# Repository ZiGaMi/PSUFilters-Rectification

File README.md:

# PSUFilters-Rectification
This repository contains KiCad project of circuit with filtering, rectification and safety elements for PSU module. Purpose of circuit is to adjust mains voltage to working voltage of cheap PSU modules. In this case PSU module DP50V5A is used, but other modules can be used with same circuit as well.

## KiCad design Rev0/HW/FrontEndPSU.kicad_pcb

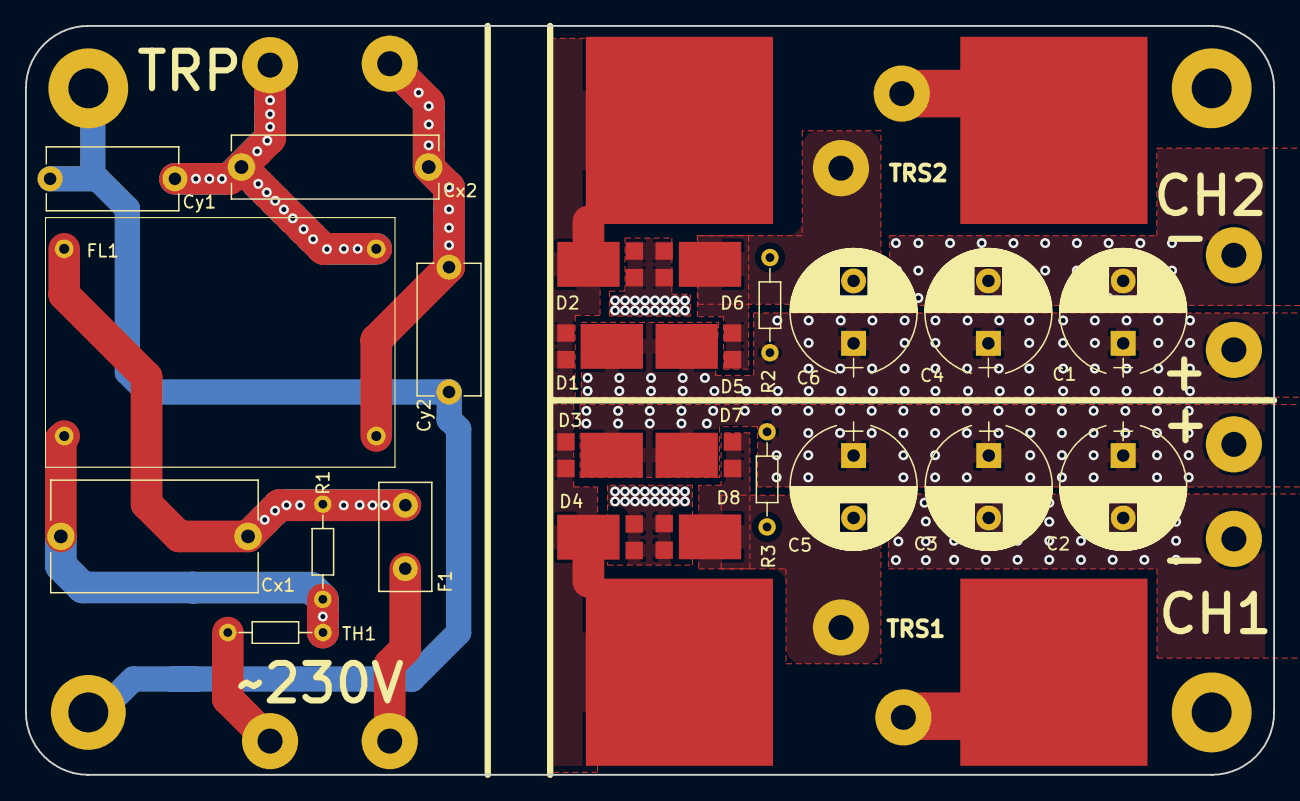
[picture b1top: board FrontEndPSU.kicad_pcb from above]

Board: 2 copper layers, 100.0 x 60.0 mm, 29 parts (0 on the bottom side), 13 nets.

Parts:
C1, C2, C3, C4, C5, C6: 100u; CP_Radial_D10.0mm_P5.00mm
Cx1: 470n; C_Rect_L16.5mm_W8.9mm_P15.00mm_MKT
Cx2: 47n; C_Rect_L16.5mm_W5.0mm_P15.00mm_MKT
Cy1, Cy2: 2n2; C_Disc_D10.5mm_W5.0mm_P10.00mm
D1, D2, D3, D4, D5, D6, D7, D8: PMEG060V100; SOT1289
F1: 2A/230V; Fuse_TE5_Littlefuse-395Series
F2, F3: 6A; FuseHRC_10x38mm
FL1: EMI_Filter_CommonMode; CCM_Compact
J4, J5, J6: Conn_01x01; MountingHole_3.2mm_M3_Pad
R1, R2, R3: 1M; R_Axial_DIN0204_L3.6mm_D1.6mm_P7.62mm_Horizontal
TH1: Thermistor_NTC; R_Axial_DIN0204_L3.6mm_D1.6mm_P7.62mm_Horizontal

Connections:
/CH1+: C2.1, C3.1, C5.1, D3.1, D7.1, R3.1
/CH1-: C2.2, C3.2, C5.2, D4.2, D8.2, R3.2
/CH2+: C1.1, C4.1, C6.1, D1.1, D5.1, R2.1
/CH2-: C1.2, C4.2, C6.2, D2.2, D6.2, R2.2
Earth: Cy1.2, Cy2.1, J6.1
unnamed: Cx1.1, F1.1, FL1.1, R1.1
unnamed: Cx1.2, FL1.3, R1.2, TH1.1
unnamed: Cx2.1, Cy1.1, FL1.2
unnamed: Cx2.2, Cy2.2, FL1.4
unnamed: D1.2, D2.1, F2.1
unnamed: D3.2, D4.1, F3.1
unnamed: D5.2, D6.1
unnamed: D7.2, D8.1

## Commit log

2019-05-05 new file: Rev0/Docs/PSUFilters&Rectification.pdf new file: Rev0/HW/FrontEndPSU.kicad_pcb new file: Rev0/HW/FrontEndPSU.pro new file: Rev0/HW/FrontEndPSU.sch
